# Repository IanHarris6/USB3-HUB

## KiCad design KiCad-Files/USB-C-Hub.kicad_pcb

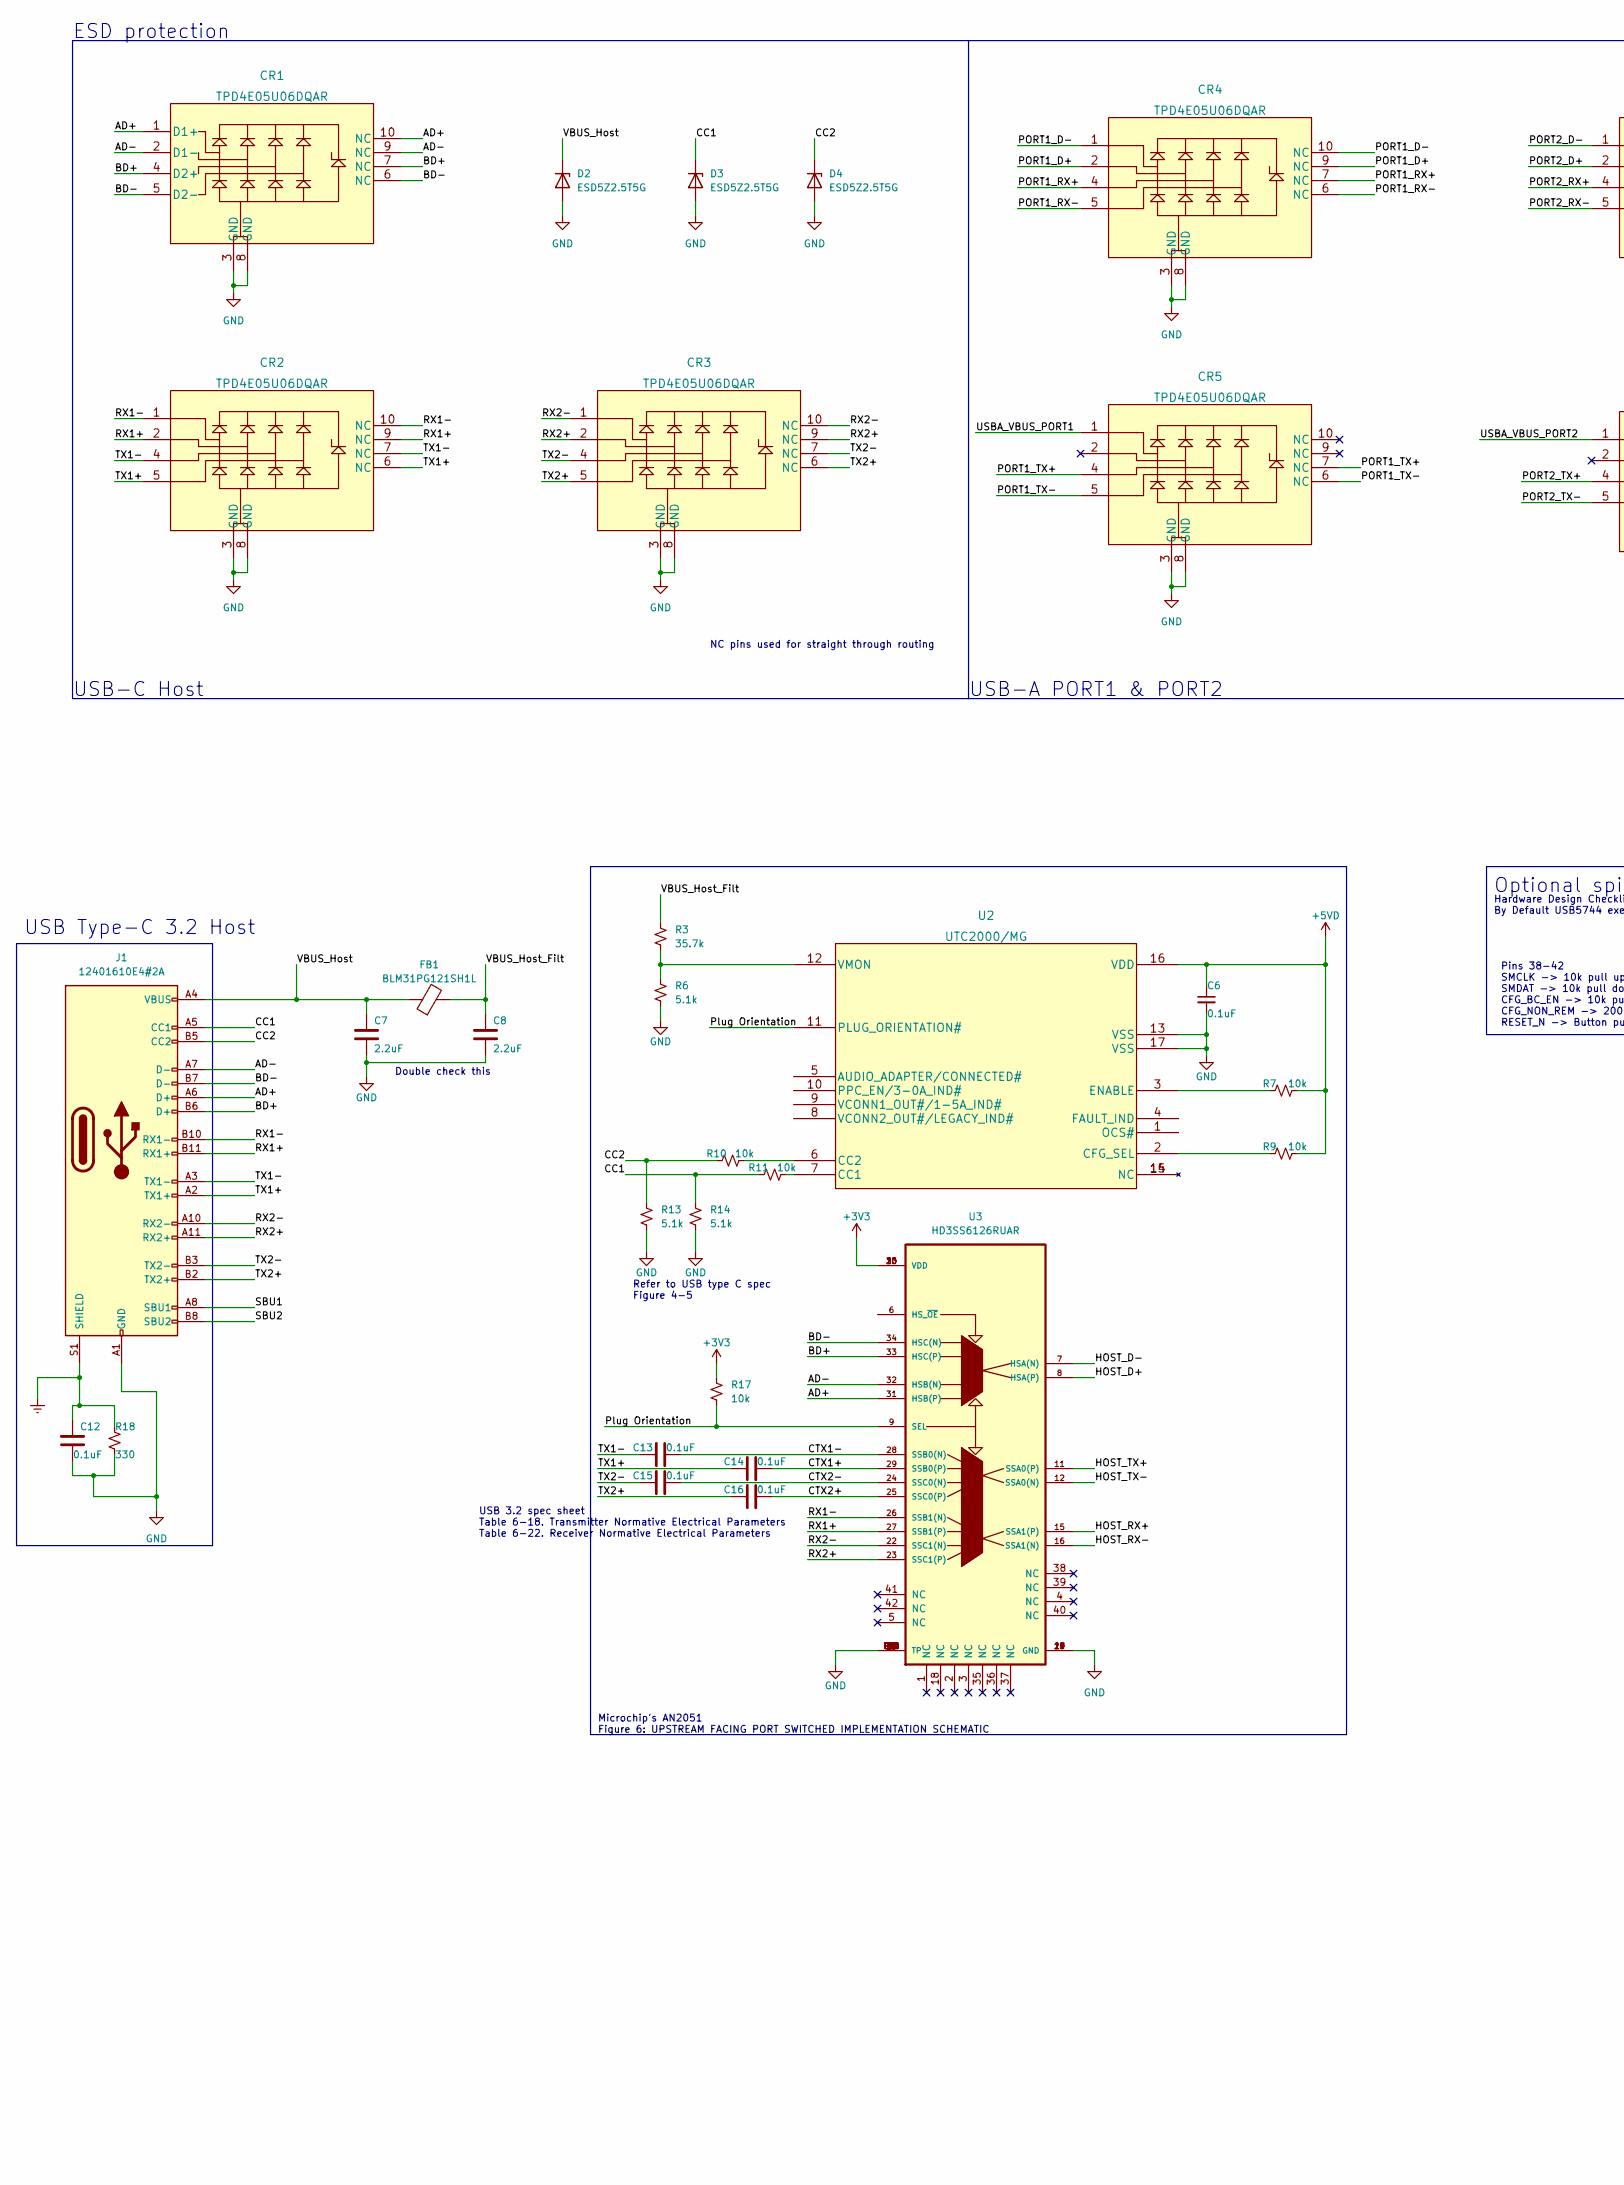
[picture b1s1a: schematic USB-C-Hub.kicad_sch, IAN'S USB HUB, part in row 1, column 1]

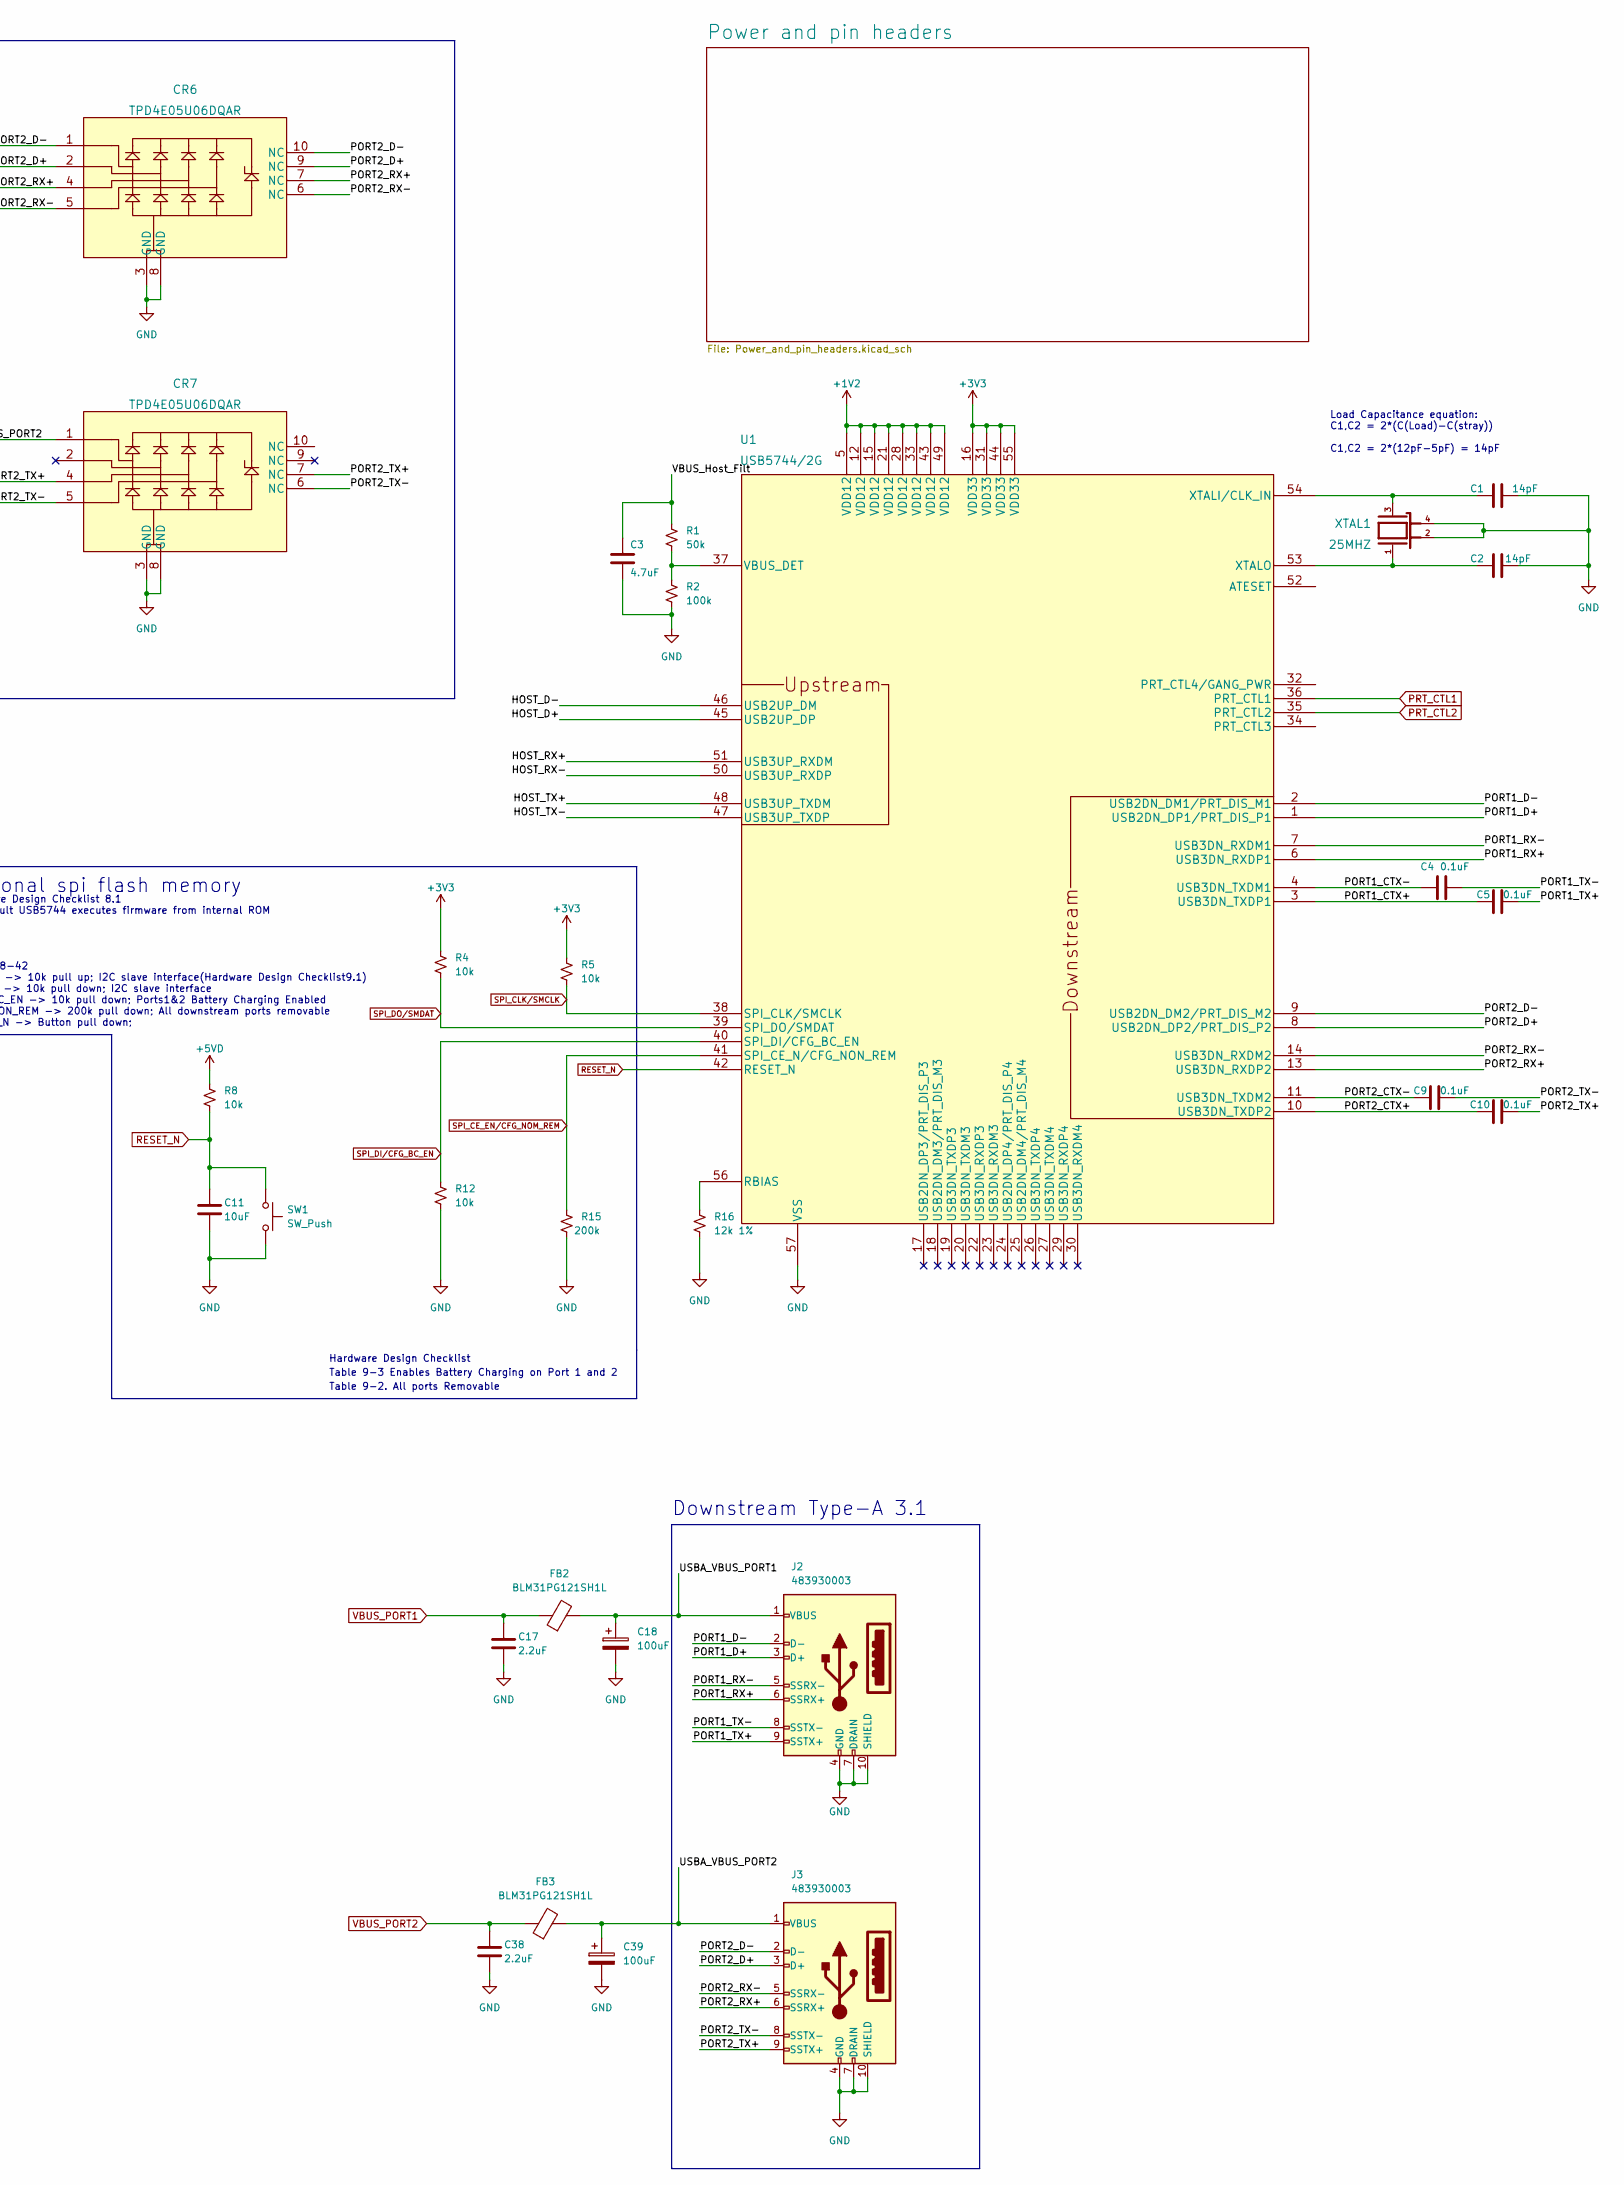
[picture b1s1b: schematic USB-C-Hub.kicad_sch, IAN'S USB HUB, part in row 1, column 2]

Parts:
C1, C2: 14pF; R_0402_1005Metric
C3: 4.7uF; C_0603_1608Metric; MFR# CL10A475KQ8NNNC
C4, C5, C6, C12, C13, C14, C15, C16: 0.1uF; C_0402_1005Metric; MFR# CL05A104KA5NNNC
C7, C8: 2.2uF; C_0603_1608Metric
C9, C10: 0.1uF; C_0402_1005Metric
C11: 10uF; C_0603_1608Metric; MFR# CL10A106KQ8NNNC
C17, C38: 2.2uF; C_0603_1608Metric; MFR# CL10A225KO8NNNC
C18: 100uF; CP_Elec_10x10.5; MFR# MAL215097101E3
C39: 100uF; CP_Elec_10x10.5; MFG# MAL215097101E3
CR1, CR2, CR3, CR4, CR5, CR6, CR7: TPD4E05U06DQAR; USON-10_2.5x1.0mm_P0.5mm
D2, D3, D4: ESD5Z2.5T5G; D_SOD-523
FB1, FB2, FB3: BLM31PG121SH1L; R_1206_3216Metric
J1: 12401610E4#2A; USB_C_Receptacle_Amphenol_12401610E4-2A
J2, J3: 483930003; USB3_A_Molex_48393-001
R1: 50k; R_0402_1005Metric
R2: 100k; R_0402_1005Metric
R3: 35.7k; R_0402_1005Metric
R4, R5, R7, R8, R9, R10, R11, R12, R17: 10k; R_0402_1005Metric
R6, R13, R14: 5.1k; R_0402_1005Metric
R15: 200k; R_0402_1005Metric; MFG# RC0402JR-07200KL
R16: 12k 1%; R_0402_1005Metric
R18: 330; R_0402_1005Metric
SW1: SW_Push; SW_SPST_PTS645; MFR# PTS645SK43SMTR92 LFS
U1: USB5744/2G; VQFN56_2G_MCH
U2: UTC2000/MG; 16-pinQFN3x3; MFR# UTC2000/MG
U3: HD3SS6126RUAR; QFN50P900X350X80-43N
XTAL1: 25MHZ; ECS-250-12-33Q-JES-TR_ECS; MFR# ECS-250-12-33Q-JES-TR

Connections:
+1V2: U1.5 (VDD12), U1.12 (VDD12), U1.15 (VDD12), U1.21 (VDD12), U1.28 (VDD12), U1.33 (VDD12), U1.43 (VDD12), U1.49 (VDD12); also elsewhere on the board
+3V3: R4.1, R5.1, R17.1, U1.16 (VDD33), U1.31 (VDD33), U1.44 (VDD33), U1.55 (VDD33), U3.13 (VDD), U3.20 (VDD), U3.30 (VDD); also elsewhere on the board
+5VD: C6.1, R7.1, R8.1, R9.1, U2.16 (VDD); also elsewhere on the board
/AD+: CR1.1 (D1+), CR1.10 (NC), J1.A6 (D+), U3.31 (HSB(P))
/AD-: CR1.2 (D1-), CR1.9 (NC), J1.A7 (D-), U3.32 (HSB(N))
/BD+: CR1.4 (D2+), CR1.7 (NC), J1.B6 (D+), U3.33 (HSC(P))
/BD-: CR1.5 (D2-), CR1.6 (NC), J1.B7 (D-), U3.34 (HSC(N))
/CC1: D3.1 (K), J1.A5 (CC1), R11.2, R14.1
/CC2: D4.1 (K), J1.B5 (CC2), R10.2, R13.1
/CTX1+: C14.2, U3.29 (SSB0(P))
/CTX1-: C13.2, U3.28 (SSB0(N))
/CTX2+: C16.2, U3.25 (SSC0(P))
/CTX2-: C15.2, U3.24 (SSC0(N))
/HOST_D+: U1.45 (USB2UP_DP), U3.8 (HSA(P))
/HOST_D-: U1.46 (USB2UP_DM), U3.7 (HSA(N))
/HOST_RX+: U1.51 (USB3UP_RXDM), U3.15 (SSA1(P))
/HOST_RX-: U1.50 (USB3UP_RXDP), U3.16 (SSA1(N))
/HOST_TX+: U1.48 (USB3UP_TXDM), U3.11 (SSA0(P))
/HOST_TX-: U1.47 (USB3UP_TXDP), U3.12 (SSA0(N))
/PORT1_CTX+: C5.1, U1.3 (USB3DN_TXDP1)
/PORT1_CTX-: C4.1, U1.4 (USB3DN_TXDM1)
/PORT1_D+: CR4.2, CR4.9 (NC), J2.3 (D+), U1.1 (USB2DN_DP1/PRT_DIS_P1)
/PORT1_D-: CR4.1, CR4.10 (NC), J2.2 (D-), U1.2 (USB2DN_DM1/PRT_DIS_M1)
/PORT1_RX+: CR4.4, CR4.7 (NC), J2.6 (SSRX+), U1.6 (USB3DN_RXDP1)
/PORT1_RX-: CR4.5, CR4.6 (NC), J2.5 (SSRX-), U1.7 (USB3DN_RXDM1)
/PORT1_TX+: C5.2, CR5.4, CR5.7 (NC), J2.9 (SSTX+)
/PORT1_TX-: C4.2, CR5.5, CR5.6 (NC), J2.8 (SSTX-)
/PORT2_CTX+: C10.1, U1.10 (USB3DN_TXDP2)
/PORT2_CTX-: C9.1, U1.11 (USB3DN_TXDM2)
/PORT2_D+: CR6.2, CR6.9 (NC), J3.3 (D+), U1.8 (USB2DN_DP2/PRT_DIS_P2)
/PORT2_D-: CR6.1, CR6.10 (NC), J3.2 (D-), U1.9 (USB2DN_DM2/PRT_DIS_M2)
/PORT2_RX+: CR6.4, CR6.7 (NC), J3.6 (SSRX+), U1.13 (USB3DN_RXDP2)
/PORT2_RX-: CR6.5, CR6.6 (NC), J3.5 (SSRX-), U1.14 (USB3DN_RXDM2)
/PORT2_TX+: C10.2, CR7.4, CR7.7 (NC), J3.9 (SSTX+)
/PORT2_TX-: C9.2, CR7.5, CR7.6 (NC), J3.8 (SSTX-)
/Plug Orientation: R17.2, U2.11 (PLUG_ORIENTATION#), U3.9 (SEL)
/RX1+: CR2.2, CR2.9 (NC), J1.B11 (RX1+), U3.27 (SSB1(P))
/RX1-: CR2.1, CR2.10 (NC), J1.B10 (RX1-), U3.26 (SSB1(N))
/RX2+: CR3.2, CR3.9 (NC), J1.A11 (RX2+), U3.23 (SSC1(P))
/RX2-: CR3.1, CR3.10 (NC), J1.A10 (RX2-), U3.22 (SSC1(N))
/SBU1: J1.A8 (SBU1)
/SBU2: J1.B8 (SBU2)
/TX1+: C14.1, CR2.5, CR2.6 (NC), J1.A2 (TX1+)
/TX1-: C13.1, CR2.4, CR2.7 (NC), J1.A3 (TX1-)
/TX2+: C16.1, CR3.5, CR3.6 (NC), J1.B2 (TX2+)
/TX2-: C15.1, CR3.4, CR3.7 (NC), J1.B3 (TX2-)
/USBA_VBUS_PORT1: C18.1, CR5.1, FB2.2, J2.1 (VBUS)
/USBA_VBUS_PORT2: C39.1, CR7.1, FB3.2, J3.1 (VBUS)
/VBUS_Host: C7.1, D2.1 (K), FB1.1, J1.A4 (VBUS), J1.A9 (VBUS), J1.B4 (VBUS), J1.B9 (VBUS)
/VBUS_Host_Filt: C3.1, C8.1, FB1.2, R1.1, R3.1
Earth: C12.1, J1.S1 (SHIELD), R18.1
GND: C1.1, C2.1, C3.2, C6.2, C7.2, C8.2, C11.2, C12.2, C17.2, C18.2, C38.2, C39.2, CR1.3 (GND), CR1.8 (GND), CR2.3 (GND), CR2.8 (GND), CR3.3 (GND), CR3.8 (GND), CR4.3 (GND), CR4.8 (GND), CR5.3 (GND), CR5.8 (GND), CR6.3 (GND), CR6.8 (GND), CR7.3 (GND), CR7.8 (GND), D2.2 (A), D3.2 (A), D4.2 (A), J1.A1 (GND), J1.A12 (GND), J1.B1 (GND), J1.B12 (GND), J2.4 (GND), J2.7 (DRAIN), J2.10 (SHIELD), J3.4 (GND), J3.7 (DRAIN), J3.10 (SHIELD), R2.2, R6.2, R12.2, R13.2, R14.2, R15.2, R16.2, R18.2, SW1.2, U1.57 (VSS), U2.13 (VSS), U2.17 (VSS), U3.10 (GND), U3.14 (GND), U3.17 (GND), U3.19 (GND), U3.21 (GND), U3.43 (TP), U3.E1 (TP), U3.E2 (TP), U3.E3 (TP), U3.E4 (TP), U3.E5 (TP), U3.E6 (TP), U3.E7 (TP), U3.E8 (TP), U3.E9 (TP), U3.E10 (TP), U3.E11 (TP), U3.E12 (TP), U3.E13 (TP), U3.E14 (TP), XTAL1.2, XTAL1.4; also elsewhere on the board
unnamed: C1.2, U1.54 (XTALI/CLK_IN), XTAL1.3
unnamed: C2.2, U1.53 (XTALO), XTAL1.1
unnamed: R1.2, R2.1, U1.37 (VBUS_DET)
unnamed: R3.2, R6.1, U2.12 (VMON)
unnamed: R7.2, U2.3 (ENABLE)
unnamed: R9.2, U2.2 (CFG_SEL)
unnamed: R10.1, U2.6 (CC2)
unnamed: R11.1, U2.7 (CC1)
unnamed: R16.1, U1.56 (RBIAS)
PRT_CTL1: U1.36 (PRT_CTL1); also elsewhere on the board
PRT_CTL2: U1.35 (PRT_CTL2); also elsewhere on the board
RESET_N: C11.1, R8.2, SW1.1, U1.42 (RESET_N); also elsewhere on the board
SPI_CE_EN/CFG_NOM_REM: R15.1, U1.41 (SPI_CE_N/CFG_NON_REM); also elsewhere on the board
SPI_CLK/SMCLK: R5.2, U1.38 (SPI_CLK/SMCLK); also elsewhere on the board
SPI_DI/CFG_BC_EN: R12.1, U1.40 (SPI_DI/CFG_BC_EN); also elsewhere on the board
SPI_DO/SMDAT: R4.2, U1.39 (SPI_DO/SMDAT); also elsewhere on the board
VBUS_PORT1: C17.1, FB2.1; also elsewhere on the board
VBUS_PORT2: C38.1, FB3.1; also elsewhere on the board

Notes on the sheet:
ESD protection
Load Capacitance equation: C1,C2 = 2*(C(Load)-C(stray)) C1,C2 = 2*(12pF-5pF) = 14pF
USB 3.2 spec sheet Table 6-18. Transmitter Normative Electrical Parameters Table 6-22. Receiver Normative Electrical Parameters
Downstream Type-A 3.1
Refer to USB type C spec Figure 4-5
Pins 38-42 SMCLK -> 10k pull up; I2C slave interface(Hardware Design Checklist9.1) SMDAT -> 10k pull down; I2C slave interface CFG_BC_EN -> 10k pull down; Ports1&2 Battery Charging Enabled CFG_NON_REM -> 200k pull down; All downstream ports removable RESET_N -> Button pull down;
Optional spi flash memory
USB-C Host
USB Type-C 3.2 Host
Table 9-3 Enables Battery Charging on Port 1 and 2
NC pins used for straight through routing
Table 9-2. All ports Removable
Hardware Design Checklist 8.1 By Default USB5744 executes firmware from internal ROM
Hardware Design Checklist
USB-A PORT1 & PORT2
Double check this
Microchip's AN2051 Figure 6: UPSTREAM FACING PORT SWITCHED IMPLEMENTATION SCHEMATIC

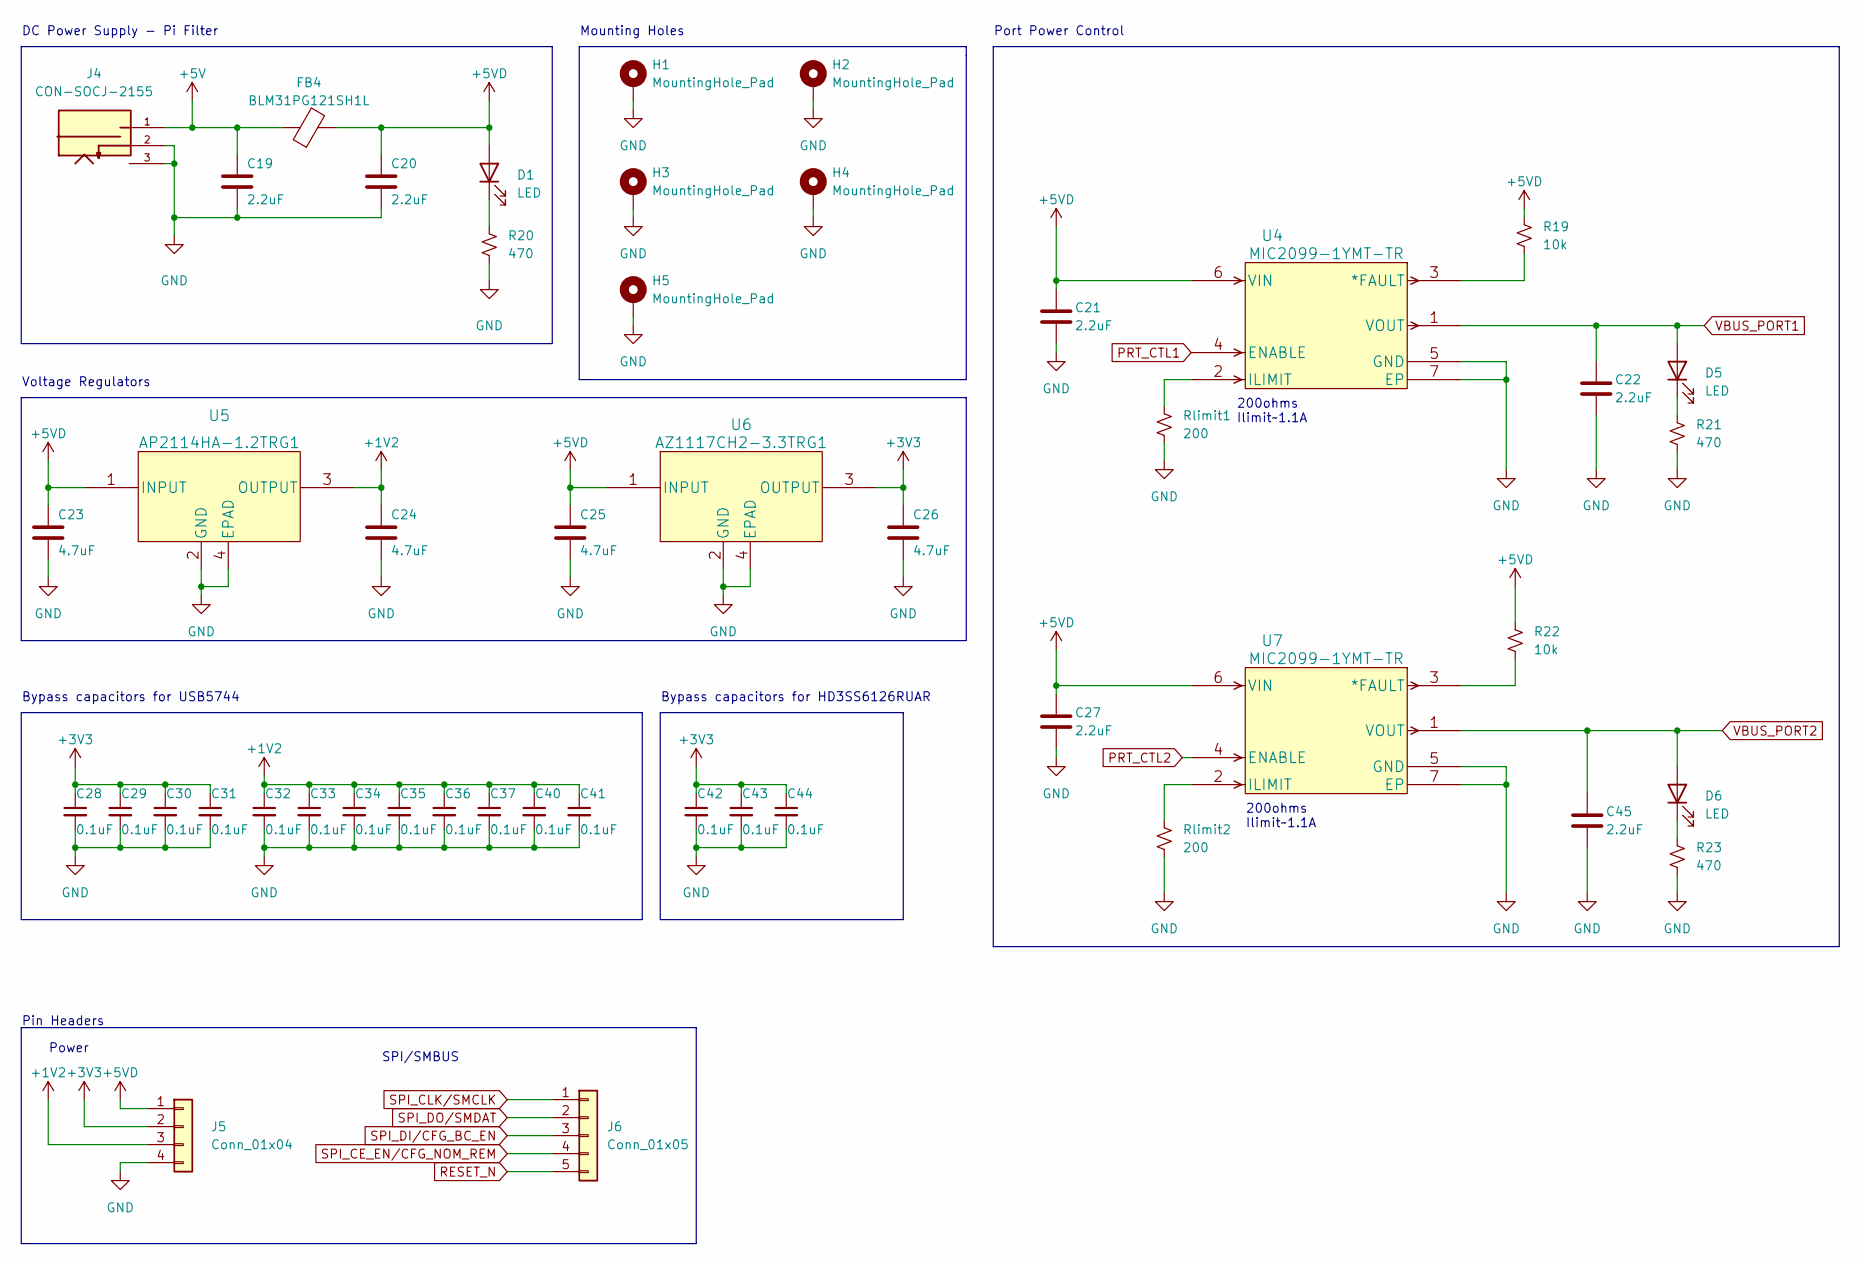
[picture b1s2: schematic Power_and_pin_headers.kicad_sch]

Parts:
C19, C20, C21, C22, C27, C45: 2.2uF; C_0603_1608Metric; MFR# CL10A225KO8NNNC
C23, C24, C25, C26: 4.7uF; C_0603_1608Metric; MFR# CL10A475KQ8NNNC
C28, C29, C30, C31, C32, C33, C34, C35, C36, C37, C40, C41, C42, C43, C44: 0.1uF; C_0402_1005Metric; MFR# CL05A104KA5NNNC
D1, D5, D6: LED; LED_0603_1608Metric; MFR# LTST-C191KRKT
FB4: BLM31PG121SH1L; R_1206_3216Metric
H1, H2, H3, H4, H5: MountingHole_Pad; MountingHole_3mm_Pad_Via
J4: CON-SOCJ-2155; GRAVITECH_CON-SOCJ-2155; PARTREV NA
J5: Conn_01x04; PinSocket_1x04_P2.54mm_Vertical
J6: Conn_01x05; PinSocket_1x05_P2.54mm_Vertical
R19, R22: 10k; R_0402_1005Metric
R20, R21, R23: 470; R_0402_1005Metric; MFR# WR04X4700FTL
Rlimit1, Rlimit2: 200; R_0402_1005Metric
U4, U7: MIC2099-1YMT-TR; TMLF-6_MT_MCH
U5: AP2114HA-1.2TRG1; SOT-223
U6: AZ1117CH2-3.3TRG1; SOT-223

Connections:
+1V2: C24.1, C32.1, C33.1, C34.1, C35.1, C36.1, C37.1, C40.1, C41.1, J5.3, U5.3 (OUTPUT); also elsewhere on the board
+3V3: C26.1, C28.1, C29.1, C30.1, C31.1, C42.1, C43.1, C44.1, J5.2, U6.3 (OUTPUT); also elsewhere on the board
+5V: C19.1, FB4.1, J4.1
+5VD: C20.1, C21.1, C23.1, C25.1, C27.1, D1.2 (A), FB4.2, J5.1, R19.1, R22.1, U4.6 (VIN), U5.1 (INPUT), U6.1 (INPUT), U7.6 (VIN); also elsewhere on the board
GND: C19.2, C20.2, C21.2, C22.2, C23.2, C24.2, C25.2, C26.2, C27.2, C28.2, C29.2, C30.2, C31.2, C32.2, C33.2, C34.2, C35.2, C36.2, C37.2, C40.2, C41.2, C42.2, C43.2, C44.2, C45.2, H1.1, H2.1, H3.1, H4.1, H5.1, J4.2, J4.3, J5.4, R20.2, R21.2, R23.2, Rlimit1.2, Rlimit2.2, U4.5 (GND), U4.7 (EP), U5.2 (GND), U5.4 (EPAD), U6.2 (GND), U6.4 (EPAD), U7.5 (GND), U7.7 (EP); also elsewhere on the board
unnamed: D1.1 (K), R20.1
unnamed: D5.1 (K), R21.1
unnamed: D6.1 (K), R23.1
unnamed: R19.2, U4.3 (*FAULT)
unnamed: R22.2, U7.3 (*FAULT)
unnamed: Rlimit1.1, U4.2 (ILIMIT)
unnamed: Rlimit2.1, U7.2 (ILIMIT)
PRT_CTL1: U4.4 (ENABLE); also elsewhere on the board
PRT_CTL2: U7.4 (ENABLE); also elsewhere on the board
RESET_N: J6.5; also elsewhere on the board
SPI_CE_EN/CFG_NOM_REM: J6.4; also elsewhere on the board
SPI_CLK/SMCLK: J6.1; also elsewhere on the board
SPI_DI/CFG_BC_EN: J6.3; also elsewhere on the board
SPI_DO/SMDAT: J6.2; also elsewhere on the board
VBUS_PORT1: C22.1, D5.2 (A), U4.1 (VOUT); also elsewhere on the board
VBUS_PORT2: C45.1, D6.2 (A), U7.1 (VOUT); also elsewhere on the board

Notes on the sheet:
DC Power Supply - Pi Filter
Power
200ohms Ilimit~1.1A
SPI/SMBUS
Bypass capacitors for USB5744
Pin Headers
Port Power Control
Mounting Holes
Bypass capacitors for HD3SS6126RUAR
Voltage Regulators

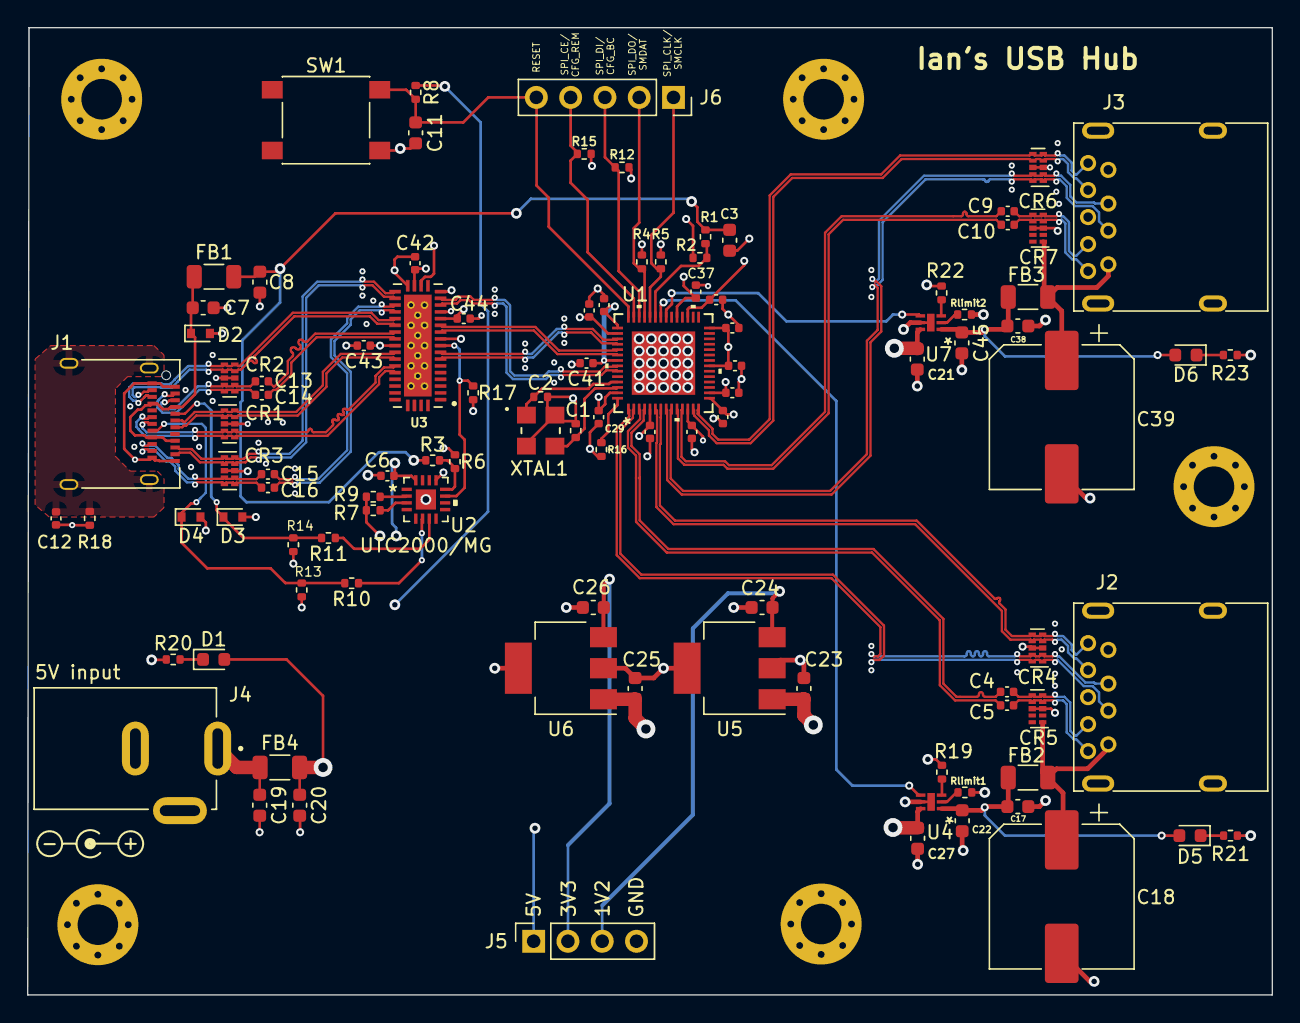
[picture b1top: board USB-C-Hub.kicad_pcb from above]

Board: 4 copper layers, 92.2 x 71.7 mm, 107 parts (0 on the bottom side), 76 nets.

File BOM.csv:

Qty,Reference(s),Value,Item Description,Footprint,MANUFACTURER,MFR#,Digikey Listing,Datasheet,Spec,Sample
2,"C1, C2",14pF,Capacitor,R_0402_1005Metric,,,,,,
5,"C3, C23, C24, C25, C26",4.7uF,Capacitor,C_0603_1608Metric,,CL10A475KQ8NNNC,https://www.digikey.com/en/products/detail/samsung-electro-m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,,,
25,"C4, C5, C9, C10, C12, C13, C14, C15, C16, C6, C28, C29, C30, C31, C32, C33, C34, C35, C36, C37, C40, C41, C42, C43, C44",0.1uF,Capacitor,C_0402_1005Metric,,CL05A104KA5NNNC,,,,
10,"C7, C8, C17, C19, C20, C21, C22, C27, C38, C45",2.2uF,Capacitor,C_0603_1608Metric,,CL10A225KO8NNNC,,,,
1,C11,10uF,Capacitor,C_0603_1608Metric,,CL10A106KQ8NNNC,https://www.digikey.com/en/products/detail/samsung-electro-m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,,,
2,"C18, C39",100uF,Capacitor,CP_Elec_10x10.5,,MAL215097101E3,https://www.digikey.com/en/products/detail/vishay-beyschlag-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,https://www.vishay.com/docs/28395/150crz.pdf,,
7,"CR1, CR2, CR3, CR4, CR5, CR6, CR7",TPD4E05U06DQAR,ESD Diode Array,USON-10_2.5x1.0mm_P0.5mm,,TPD4E05U06DQAR,https://www.digikey.com/en/products/detail/texas-instruments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,,,
3,"D1, D5, D6",LED,Red LED,LED_0603_1608Metric,,LTST-C191KRKT,https://www.digikey.com/en/products/detail/liteon/LTST-C191K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,,,
3,"D2, D3, D4",ESD5Z2.5T5G,Single ESD Diode,D_SOD-523,,ESD5Z2.5T5G,https://www.digikey.com/en/products/detail/onsemi/ESD5Z2-5T5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,https://www.onsemi.com/pdf/datasheet/esd5z2.5t1-d.pdf,,
4,"FB1, FB2, FB3, FB4",BLM31PG121SH1L,FerriteBead,1206_3216Metric,,BLM31PG121SH1L,https://www.digikey.com/en/products/detail/murata-electronic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,,,https://www.amphenol-cs.com/usb-3-2-gen2-12401610e42a.html
1,J1,12401610E4#2A,USB_C_Receptacle,USB_C_Receptacle_Amphenol_12401610E4-2A,,12401610E4#2A,https://www.digikey.com/en/products/detail/amphenol-icc-comm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,,https://www.usb.org/sites/default/files/USB%20Type-C%20Spec%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,
2,"J2, J3",483930003,USB3_A,USB3_A_Molex_48393-001,,483930003,https://www.digikey.com/en/products/detail/molex/0483930003/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,,,https://www.molex.com/molex/products/part-detail/io_connecto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
1,J4,CON-SOCJ-2155,CON-SOCJ-2155,GRAVITECH_CON-SOCJ-2155,Gravitech,CON-SOCJ-2155,https://www.mouser.com/ProductDetail/Gravitech/CON-SOCJ-2155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,,,
1,R1,50kΩ,Resistor,R_0402_1005Metric,,,https://www.digikey.com/en/products/detail/yageo/RT1206BRD07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,,,
1,R2,100kΩ,Resistor,R_0402_1005Metric,,,https://www.digikey.com/en/products/detail/yageo/RC0402FR-07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,,,
1,R3,35.7kΩ,Resistor,R_0402_1005Metric,,,https://www.digikey.com/en/products/detail/yageo/RT1206BRD07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,,,
11,"R4, R5, R7, R8, R9, R10, R11, R12, R17, R19, R22",10kΩ,Resistor,R_0402_1005Metric,,RC0402JR-0710KL,https://www.digikey.com/en/products/detail/yageo/RC0402JR-07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,,,
3,"R6, R13, R14",5.1kΩ,Resistor,R_0402_1005Metric,,,https://www.digikey.com/en/products/detail/yageo/RT1206BRD07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,,,
1,R15,200kΩ,Resistor,R_0402_1005Metric,,RC0402JR-07200KL,https://www.digikey.com/en/products/detail/yageo/RC0402JR-07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,,,
1,R16,12kΩ 1%,Resistor,R_0402_1005Metric,,RC0402FR-0712KL,https://www.digikey.com/en/products/detail/yageo/RC0402FR-07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,,,
1,R18,330Ω,Resistor,R_0402_1005Metric,,WR04X331 JTL,https://www.digikey.com/en/products/detail/walsin-technology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,,,
3,"R20, R21, R23",470Ω,Resistor,R_0402_1005Metric,,WR04X4700FTL,https://www.digikey.com/en/products/detail/walsin-technology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,,,
2,"Rlimit1, Rlimit2",200Ω,Resistor,R_0402_1005Metric,,,~,,,
1,SW1,SW_Push,Push Button,SW_SPST_PTS645,,PTS645SK43SMTR92 LFS,https://www.digikey.com/en/products/detail/c-k/PTS645SK43SMT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,,,
1,U1,USB5744/2G,USB Hub,VQFN56_2G_MCH,,USB5744/2G,https://www.digikey.com/en/products/detail/microchip-technol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,,,
1,U2,UTC2000/MG,USB type-C controller,16-pinQFN3x3,,UTC2000/MG,https://www.digikey.com/en/products/detail/microchip-technol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,,,https://www.microchipdirect.com/product/UTC2000-E/MG?samples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
1,U3,HD3SS6126RUAR,USB Mux,QFN50P900X350X80-43N,,HD3SS6126RUAR,https://www.digikey.com/en/products/detail/texas-instruments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,,,
2,"U4, U7",MIC2099-1YMT-TR,Load switch,TMLF-6_MT_MCH,,MIC2099-1YMT-TR,https://www.mouser.com/ProductDetail/Microchip-Technology/MI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,,,
1,U5,AP2114HA-1.2TRG1,1.2V Regulator,SOT-223,,AP2114HA-1.2TRG1,https://www.digikey.com/en/products/detail/diodes-incorporat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,,,
1,U6,AZ1117CH2-3.3TRG1,3.3V Regulator,SOT-223,,AZ1117CH2-3.3TRG1,https://www.digikey.com/en/products/detail/diodes-incorporat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,,,
1,XTAL1,25MHZ,Crystal Oscillator,ECS-250-12-33Q-JES-TR_ECS,,ECS-250-12-33Q-JES-TR,https://www.digikey.com/en/products/detail/ecs-inc/ECS-250-1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,,,

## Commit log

2023-05-25 Schematic and PCB first commit
2023-05-28 Create test
2023-05-29 Create placeholder
2023-05-29 Commiting Symbols
2023-09-13 Create gerbers
2023-09-13 Adding Gerber Files
2023-09-19 Added silkscreen and made power planes a bit wider
2023-09-19 Added silkscreen
    also made power planes a little bit wider
2023-09-19 Removed note and created new directory
2023-09-19 Upload BOM
2023-09-19 Added Silkscreen
    Widened power planes a little
2023-09-25 Add Schematics

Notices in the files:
parts and their libraries:
Copyright 2021 Accelerated Designs. All rights reserved.
